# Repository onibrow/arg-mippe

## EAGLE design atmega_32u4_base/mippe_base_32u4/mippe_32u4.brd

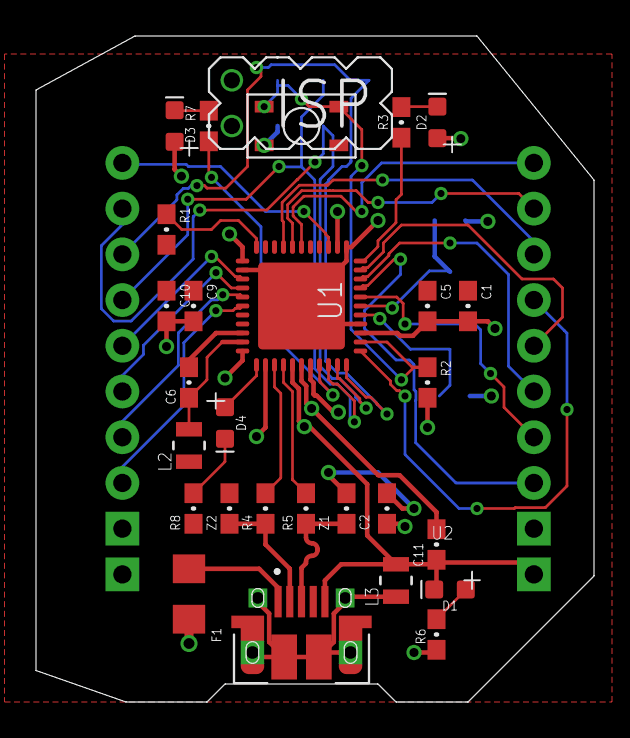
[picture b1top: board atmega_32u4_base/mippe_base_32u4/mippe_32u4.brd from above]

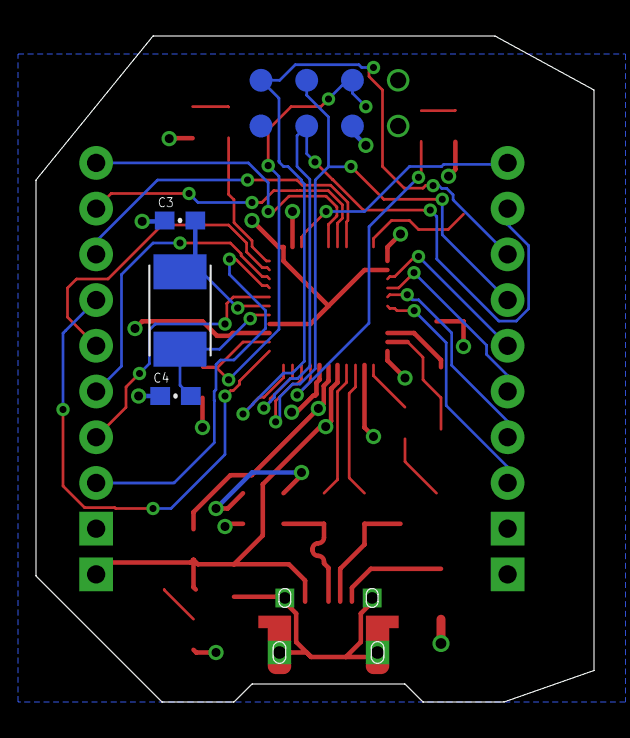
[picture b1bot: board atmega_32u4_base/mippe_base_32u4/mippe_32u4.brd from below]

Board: 2 copper layers, 31.0 x 37.0 mm, 32 parts (3 on the bottom side), 38 nets.

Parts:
C1, C2, C6, C9: 0.1uF; 0603-CAP
C3, C4: 18pF; 0603-CAP
C5, C10, C11: 1uF; 0603-CAP
D1: GREEN; LED-0603
D2, D3, D4: LED-0603
F1: 500mA; 1206
J2: USB; FCI_10103594-0001LF
J5: BURNIN
L2, L3: IND_2012
R1, R2: 10k; 0603-RES
R3, R7, R8: 330R; 0603-RES
R4, R5: 22R; 0603-RES
R6: 1K; 0603-RES
SW1: BTN-PTS810; BTN_PTS810
U1: ATMEGA32U4-XUMU; QFN44ML7X7
U2: MIPPE
Y1: 16MHz; XTAL500X320X130N
Z1, Z2: CG0603MLC-05E; 0603-RES

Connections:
5V: C1.2, C2.2, C5.2, C9.2, C10.2, D2.A, D3.A, F1.2, J5.3.3V, R2.2, R6.2, U1.2, U1.7, U1.14, U1.24, U1.34, U1.44, U2.VCC, U2.VCC@1
A0: U1.36, U2.ADC0
A1: U1.37, U2.ADC1
A2: U1.38, U2.ADC2
A3: U1.39, U2.ADC3
AGND: C6.1, L2.2, U1.43
AREF: C6.2, U1.42
D0/RX: U1.20, U2.RX
D1/TX: U1.21, U2.TX
D2/SDA: U1.19, U2.SDA
D3/SCL: U1.18, U2.SCL
D4: U1.25, U2.SS
D7: D4.A, U1.1
D_N: J2.2, R4.1, Z2.1
D_P: J2.3, R5.1, Z1.1
GND: C1.1, C2.1, C3.1, C4.1, C5.1, C9.1, C10.1, C11.1, D1.C, J2.5, J5.GND, L2.1, L3.2, R1.2, R8.1, SW1.1, SW1.2, U1.5, U1.15, U1.23, U1.35, U1.EXP, U2.GND@0, U2.GND@1, Z1.2, Z2.2
HWB: R1.1, U1.33
IO8: U1.28, U2.GPIO3
IO9*: U1.29, U2.GPIO4
IO10*: U1.30, U2.GPIO5
IO11*: U1.12, U2.GPIO6
MISO: J5.MISO, U1.11, U2.MISO
MOSI: J5.MOSI, U1.10, U2.MOSI
unnamed: D2.C, R3.2
unnamed: D3.C, R7.2
unnamed: D1.A, R6.1
unnamed: D4.C, R8.2
RD_N: R4.2, U1.3
RD_P: R5.2, U1.4
RESET: J5.RST, R2.1, SW1.3, SW1.4, U1.13
RXLED: R7.1, U1.8
SCK: J5.SCK, U1.9, U2.SCK
SHIELD: J2.S1, J2.S2, J2.S3, J2.S4, J2.S5, J2.S6, L3.1
TXLED: R3.1, U1.22
UCAP: C11.2, U1.6
XTAL1: C3.2, U1.17, Y1.1
XTAL2: C4.2, U1.16, Y1.2
XUSB: F1.1, J2.1

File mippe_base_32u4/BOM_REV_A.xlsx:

Comment | Designator | Footprint | LCSC Part #（optional）
1uF | C5, C10, C11 | 0603_C | C15849
0.1uF | C1, C2, C6, C9 | 0603_C | C14663
10k | R1, R2 | 0603_R | C25804
330 | R3, R7, R8 | 0603_R | C23138
1k | R6 | 0603_R | C21190
22 | R4, R5 | 0603_R | C23345
ATMEGA32U4 | U1 | QFN-44_EP_7x7x0.5P | C112161

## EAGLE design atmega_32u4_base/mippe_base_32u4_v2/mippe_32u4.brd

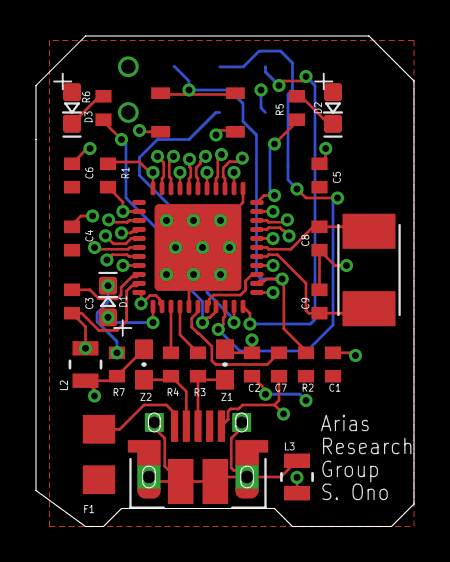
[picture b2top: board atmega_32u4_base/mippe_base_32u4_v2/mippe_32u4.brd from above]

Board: 2 copper layers, 21.0 x 27.2 mm, 29 parts (0 on the bottom side), 24 nets.

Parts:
C1, C2, C3, C4: 0.1uF; 0402-CAP
C5, C6, C7: 1uF; 0402-CAP
C8, C9: 18pF; 0402-CAP
D1, D2, D3: LED-0603
F1: 500mA; 1206
J2: USB; FCI_10103594-0001LF
J5: BURNIN
L2, L3: IND_2012
R1, R2: 10k; R0402
R3, R4: 22R; R0402
R5, R6, R7: 330R; R0402
SW1: BTN-PTS810; BTN_PTS810
U1: ATMEGA32U4-XUMU; QFN44ML7X7
Y1: 16MHz; XTAL500X320X130N
Z1, Z2: CG0603MLC-05E; 0603-RES

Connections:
5V: C1.2, C2.2, C4.2, C5.2, C6.2, D2.A, D3.A, F1.2, J5.3.3V, R2.2, U1.2, U1.7, U1.14, U1.24, U1.34, U1.44
AGND: C3.1, L2.2, U1.43
AREF: C3.2, U1.42
D7: D1.A, U1.1
D_N: J2.2, R4.1, Z2.1
D_P: J2.3, R3.1, Z1.1
GND: C1.1, C2.1, C4.1, C5.1, C6.1, C7.1, C8.1, C9.1, J2.5, J5.GND, L2.1, L3.2, R1.2, R7.1, SW1.1, SW1.2, U1.5, U1.15, U1.23, U1.35, U1.EXP, Z1.2, Z2.2
HWB: R1.1, U1.33
MISO: J5.MISO, U1.11
MOSI: J5.MOSI, U1.10
unnamed: D2.C, R5.2
unnamed: D3.C, R6.2
unnamed: D1.C, R7.2
RD_N: R4.2, U1.3
RD_P: R3.2, U1.4
RESET: J5.RST, R2.1, SW1.3, SW1.4, U1.13
RXLED: R6.1, U1.8
SCK: J5.SCK, U1.9
SHIELD: J2.S1, J2.S2, J2.S3, J2.S4, J2.S5, J2.S6, L3.1
TXLED: R5.1, U1.22
UCAP: C7.2, U1.6
XTAL1: C8.2, U1.17, Y1.1
XTAL2: C9.2, U1.16, Y1.2
XUSB: F1.1, J2.1

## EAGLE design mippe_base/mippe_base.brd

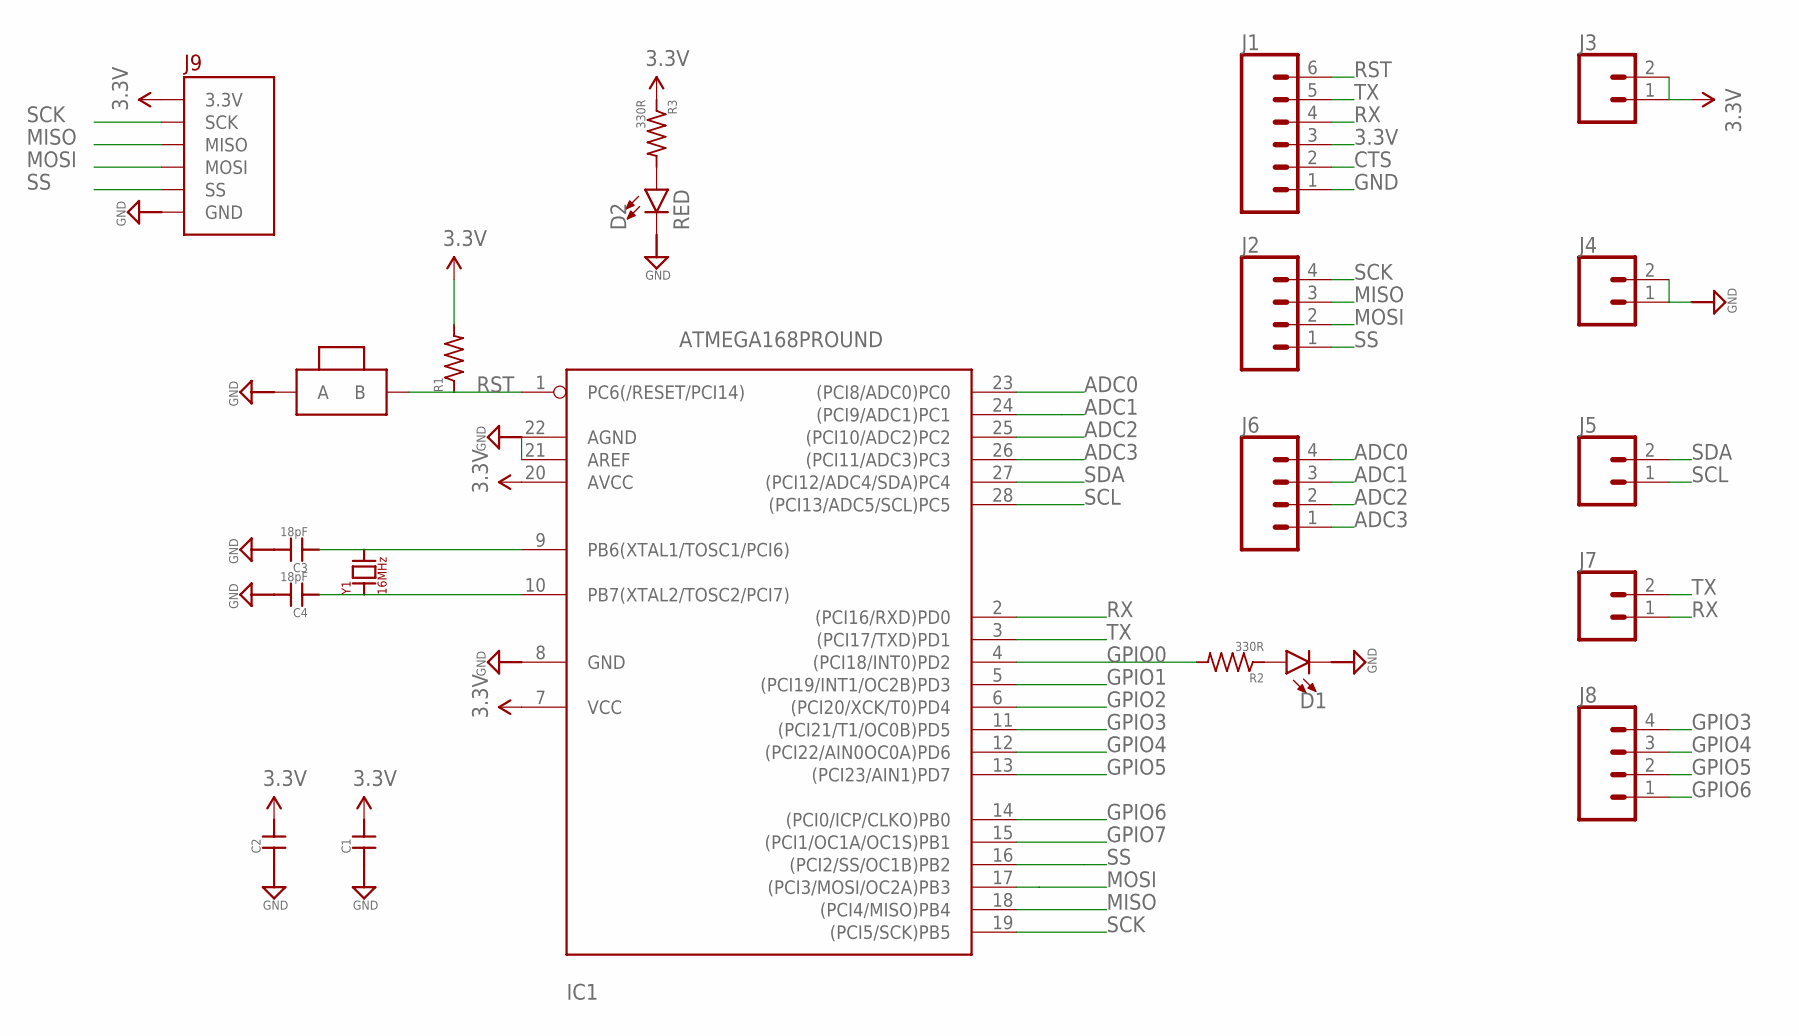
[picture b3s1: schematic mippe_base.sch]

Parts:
C1, C2: CAP0603-CAP; 0603-CAP
C3, C4: 18pF; 0603-CAP
D1: LED0603; LED-0603
D2: RED; LED-0603
IC1: ATMEGA168PROUND; DIL28-3-ROUND
J1: CONN_06NO_SILK_FEMALE_PTH; 1X06_NO_SILK
J2, J6, J8: CONN_041X04_NO_SILK; 1X04_NO_SILK
J3, J4, J5, J7: CONN_021X02_NO_SILK; 1X02_NO_SILK
J9: BURNIN
R1: R-US_R0603; R0603
R2, R3: 330R; R0603
SW1: BTN-PTS810; BTN_PTS810
Y1: 16MHz; HC-49

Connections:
3.3V: C1.2, C2.2, IC1.7 (VCC), IC1.20 (AVCC), J1.3, J3.1, J3.2, J9.3.3V, R1.2, R3.1
ADC0: IC1.23 ((PCI8/ADC0)PC0), J6.4
ADC1: IC1.24 ((PCI9/ADC1)PC1), J6.3
ADC2: IC1.25 ((PCI10/ADC2)PC2), J6.2
ADC3: IC1.26 ((PCI11/ADC3)PC3), J6.1
CTS: J1.2
GND: C1.1, C2.1, C3.2, C4.2, D1.C, D2.C, IC1.8 (GND), IC1.21 (AREF), IC1.22 (AGND), J1.1, J4.1, J4.2, J9.GND, SW1.1 (A), SW1.2 (A)
GPIO0: IC1.4 ((PCI18/INT0)PD2), R2.2
GPIO1: IC1.5 ((PCI19/INT1/OC2B)PD3)
GPIO2: IC1.6 ((PCI20/XCK/T0)PD4)
GPIO3: IC1.11 ((PCI21/T1/OC0B)PD5), J8.4
GPIO4: IC1.12 ((PCI22/AIN0OC0A)PD6), J8.3
GPIO5: IC1.13 ((PCI23/AIN1)PD7), J8.2
GPIO6: IC1.14 ((PCI0/ICP/CLKO)PB0), J8.1
GPIO7: IC1.15 ((PCI1/OC1A/OC1S)PB1)
MISO: IC1.18 ((PCI4/MISO)PB4), J2.3, J9.MISO
MOSI: IC1.17 ((PCI3/MOSI/OC2A)PB3), J2.2, J9.MOSI
unnamed: D1.A, R2.1
unnamed: D2.A, R3.2
unnamed: C3.1, IC1.9 (PB6(XTAL1/TOSC1/PCI6)), Y1.B
unnamed: C4.1, IC1.10 (PB7(XTAL2/TOSC2/PCI7)), Y1.A
RST: IC1.1 (PC6(/RESET/PCI14)), J1.6, R1.1, SW1.3 (B), SW1.4 (B)
RX: IC1.2 ((PCI16/RXD)PD0), J1.4, J7.1
SCK: IC1.19 ((PCI5/SCK)PB5), J2.4, J9.SCK
SCL: IC1.28 ((PCI13/ADC5/SCL)PC5), J5.1
SDA: IC1.27 ((PCI12/ADC4/SDA)PC4), J5.2
SS: IC1.16 ((PCI2/SS/OC1B)PB2), J2.1, J9.SS
TX: IC1.3 ((PCI17/TXD)PD1), J1.5, J7.2

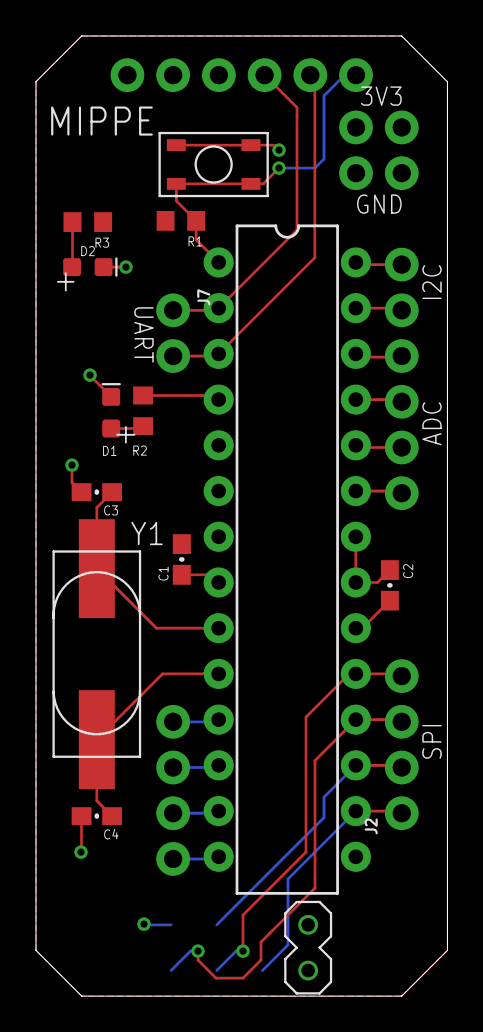
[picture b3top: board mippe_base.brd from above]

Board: 2 copper layers, 22.9 x 53.3 mm, 21 parts (0 on the bottom side), 24 nets.

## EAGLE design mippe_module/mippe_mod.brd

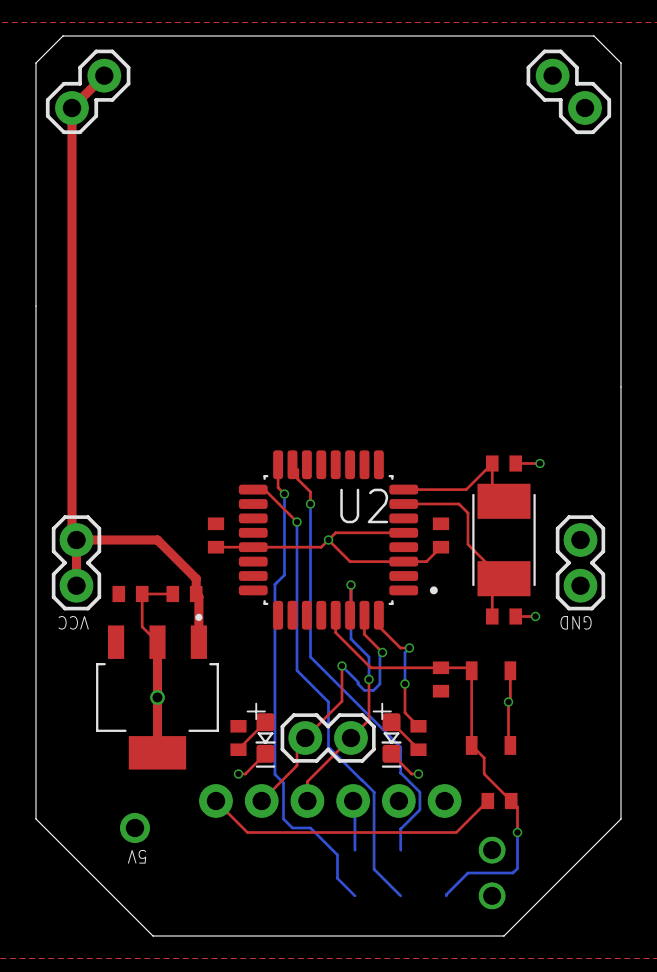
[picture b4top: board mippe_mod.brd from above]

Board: 2 copper layers, 32.5 x 50.0 mm, 24 parts (0 on the bottom side), 15 nets.

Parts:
C1, C2, C3, C4, C7: 100nF; 0402-CAP
C5, C6: 18pF; 0402-CAP
D1: LED-0603
D2: RED; LED-0603
J1, J5: VCC; 1X02
J2, J6: GND; 1X02
J3: UART; 1X02
J4: FTDI; 1X06_NO_SILK
J12: BURNIN
R1: 10k; R0402
R2, R3: 500R; R0402
SW1: BTN-PTS810; BTN_PTS810
TP1: TEST_POINTTHRU; TEST_POINT
U1: LM340MPX-5.0230; SOT230P700X180-4N
U2: ATMEGA328P-AUR; QFP80P900X900X120-32N
Y1: 16MHz; XTAL500X320X130N

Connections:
5V: C2.2, C3.2, C4.2, J4.4, J12.3.3V, R1.2, R3.1, TP1.1, U1.3, U2.4, U2.6, U2.18
GND: C1.1, C2.1, C3.1, C4.1, C5.2, C6.2, D1.C, D2.C, J2.1, J2.2, J4.6, J6.1, J6.2, J12.GND, SW1.1, SW1.2, U1.2, U1.4, U2.3, U2.5, U2.21
GPIO0: R2.2, U2.32
MISO: J12.MISO, U2.16
MOSI: J12.MOSI, U2.15
unnamed: D1.A, R2.1
unnamed: D2.A, R3.2
unnamed: C7.2, J4.1
RST: C7.1, J12.RST, R1.1, SW1.3, SW1.4, U2.29
RX: J3.1, J4.3, U2.30
SCK: J12.SCK, U2.17
TX: J3.2, J4.2, U2.31
VCC: C1.2, J1.1, J1.2, J5.1, J5.2, U1.1
XTAL1: C5.1, U2.7, Y1.2
XTAL2: C6.1, U2.8, Y1.1

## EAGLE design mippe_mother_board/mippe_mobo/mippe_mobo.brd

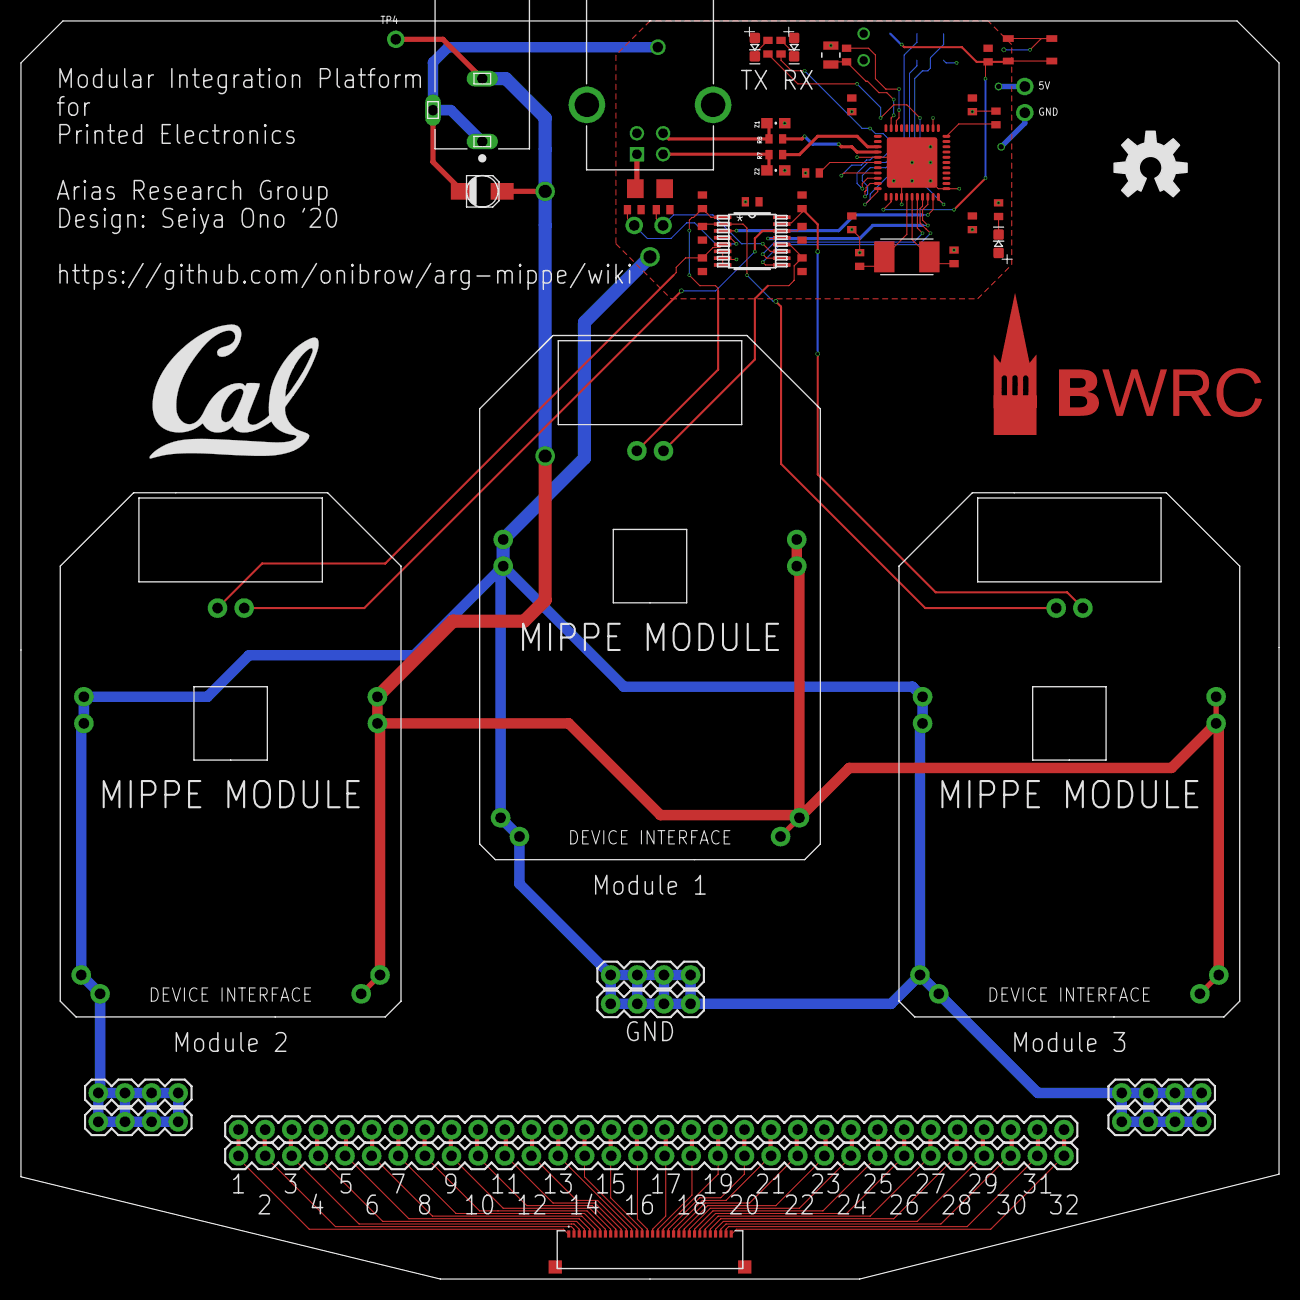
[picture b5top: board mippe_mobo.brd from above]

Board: 2 copper layers, 120.0 x 120.0 mm, 58 parts (0 on the bottom side), 67 nets.

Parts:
B1, B2, B3: MIPPE_MOD
C1, C2, C3, C4: 0.1uF; 0402-CAP
C5, C6, C7: 1uF; 0402-CAP
C8: CAP_3MM
C9, C10: 18pF; 0402-CAP
D1, D2, D3: LED-0603
F1: 500mA; 1206
J1, J2: 1X32
J3: FFC-32; MOLEX_503480-3200
J4: PJ-102AH; CUI_PJ-102AH
J5: BURNIN
J6, J7, J8, J9, J10, J11: 1X04
L1: UCB_CAL500MIL; UCB_CAL_500MIL
L2: IND_2012
R1, R2, R3, R4, R5, R6, R9, R10, R13, R14: 10k; R0402
R7, R8: 22R; R0402
R11, R12, R15: 330R; R0402
SW1: BTN-PTS810; BTN_PTS810
TP1, TP2, TP3, TP4, TP5: TEST_POINTTHRU; TEST_POINT
U1: CD4052BPWR; PW16
U3: ATMEGA32U4-XUMU; QFN44ML7X7
U$17: OSHW-LOGO-L
X1: USB-B1HSB6; OST_USB-B1HSB6
Y1: 16MHz; XTAL500X320X130N
Z1, Z2: CG0603MLC-05E; 0603-RES

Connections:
5V: C1.2, C2.2, C4.2, C5.2, C6.2, D1.A, D2.A, D3.A, F1.2, J5.3.3V, R1.1, R2.1, R3.1, R4.1, R5.1, R6.1, R10.2, R13.2, R14.2, TP5.1, U1.16, U3.2, U3.7, U3.14, U3.24, U3.34, U3.44
A: U1.10, U3.18
AGND: C3.1, L2.2, U3.43
AREF: C3.2, U3.42
B: U1.9, U3.19
D_N: R7.1, X1.2, Z2.1
D_P: R8.1, X1.3, Z1.1
GND: B1.GND@0, B1.GND@1, B1.GND@2, B1.GND@3, B2.GND@0, B2.GND@1, B2.GND@2, B2.GND@3, B3.GND@0, B3.GND@1, B3.GND@2, B3.GND@3, C1.1, C2.1, C4.1, C5.1, C6.1, C7.1, C8.NEG, C9.1, C10.1, J4.1, J4.3, J5.GND, J6.1, J6.2, J6.3, J6.4, J7.1, J7.2, J7.3, J7.4, J8.1, J8.2, J8.3, J8.4, J9.1, J9.2, J9.3, J9.4, J10.1, J10.2, J10.3, J10.4, J11.1, J11.2, J11.3, J11.4, L2.1, R9.2, R15.1, SW1.1, SW1.2, TP3.1, U1.6, U1.7, U1.8, U3.5, U3.15, U3.23, U3.35, U3.EXP, X1.4, Z1.2, Z2.2
HWB: R9.1, U3.33
MISO: J5.MISO, U3.11
MOSI: J5.MOSI, U3.10
unnamed: J1.1, J2.1, J3.1
unnamed: J1.2, J2.2, J3.2
unnamed: J1.3, J2.3, J3.3
unnamed: J1.4, J2.4, J3.4
unnamed: J1.5, J2.5, J3.5
unnamed: J1.6, J2.6, J3.6
unnamed: J1.7, J2.7, J3.7
unnamed: J1.8, J2.8, J3.8
unnamed: J1.9, J2.9, J3.9
unnamed: J1.10, J2.10, J3.10
unnamed: J1.11, J2.11, J3.11
unnamed: J1.12, J2.12, J3.12
unnamed: J1.13, J2.13, J3.13
unnamed: J1.14, J2.14, J3.14
unnamed: J1.15, J2.15, J3.15
unnamed: J1.16, J2.16, J3.16
unnamed: J1.17, J2.17, J3.17
unnamed: J1.18, J2.18, J3.18
unnamed: J1.19, J2.19, J3.19
unnamed: J1.20, J2.20, J3.20
unnamed: J1.21, J2.21, J3.21
unnamed: J1.22, J2.22, J3.22
unnamed: J1.23, J2.23, J3.23
unnamed: J1.24, J2.24, J3.24
unnamed: J1.25, J2.25, J3.25
unnamed: J1.26, J2.26, J3.26
unnamed: J1.27, J2.27, J3.27
unnamed: J1.28, J2.28, J3.28
unnamed: J1.29, J2.29, J3.29
unnamed: J1.30, J2.30, J3.30
unnamed: J1.31, J2.31, J3.31
unnamed: J1.32, J2.32, J3.32
unnamed: D2.C, R11.2
unnamed: D3.C, R12.2
unnamed: D1.C, R15.2
RD_N: R7.2, U3.3
RD_P: R8.2, U3.4
RESET: J5.RST, R10.1, SW1.3, SW1.4, U3.13
RX: U1.13, U3.20
RX1: B1.RX, R1.2, U1.1
RX2: B2.RX, R3.2, U1.5
RX3: B3.RX, R5.2, U1.2
RX4: R14.1, TP1.1, U1.4
RXLED: R12.1, U3.8
SCK: J5.SCK, U3.9
TX: U1.3, U3.21
TX1: B1.TX, R2.2, U1.12
TX2: B2.TX, R4.2, U1.14
TX3: B3.TX, R6.2, U1.15
TX4: R13.1, TP2.1, U1.11
TXLED: R11.1, U3.22
UCAP: C7.2, U3.6
VCC: B1.VCC@0, B1.VCC@1, B1.VCC@2, B1.VCC@3, B2.VCC@0, B2.VCC@1, B2.VCC@2, B2.VCC@3, B3.VCC@0, B3.VCC@1, B3.VCC@2, B3.VCC@3, C8.POS, J4.2, TP4.1
XTAL1: C9.2, U3.17, Y1.1
XTAL2: C10.2, U3.16, Y1.2
XUSB: F1.1, X1.1
